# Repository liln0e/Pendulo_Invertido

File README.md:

# Péndulo Invertido Autocontrolado

Proyecto académico de un **péndulo invertido autocontrolado (self-balancing robot)** basado en **ESP32** y control **PID**, diseñado para mantener el equilibrio de forma autónoma mediante sensores inerciales y control en tiempo real.

---

## Descripción del proyecto

Este repositorio recoge el desarrollo de un **robot autoequilibrado de dos ruedas**, integrando diseño mecánico, electrónica y programación embebida.

El sistema utiliza un **ESP32** como unidad principal de control, un sensor **MPU6050** para estimar la inclinación y un controlador **PID** encargado de actuar sobre los motores para mantener el equilibrio.

El proyecto incluye:

- Diseño mecánico del chasis mediante modelado 3D.
- Diseño electrónico mediante una PCB personalizada en **KiCad**.
- Programación embebida sobre **ESP32**.
- Implementación de control **PID** para estabilidad del sistema.

---

## Tecnologías utilizadas

### Hardware

- ESP32 DevKitC  
- MPU6050  
- TB6612FNG  
- LM7805  
- Motores DC con reductora  
- PCB personalizada  
- Chasis impreso en 3D  

### Software y herramientas

- ESP32 / Arduino Framework  
- KiCad  
- Fusion 360  
- Control PID discreto  
- Filtro complementario  

---

## Estructura del repositorio

```txt
Proyecto_Pendulo_Invertido/
│
├── README.md
├── costes.md
├── documentacion.md
│
├── assets/
├── electronica/
├── mecanica/
└── software/
```

### Documentación principal

- [`documentacion.md`](./documentacion.md) → Explicación técnica completa del sistema.
- [`costes.md`](./costes.md) → Coste aproximado de materiales y componentes.

### Carpetas del proyecto

- [`electronica/`](./electronica/) → Diseño PCB y archivos de KiCad.
- [`mecanica/`](./mecanica/) → Diseño del chasis y fabricación.
- [`software/`](./software/) → Código del sistema de control.
- [`assets/`](./assets/) → Recursos visuales del proyecto.

---

## Integrantes del proyecto

### Carla Freire Muíño  
GitHub: [@carlafreeire](https://github.com/carlafreeire)

### Noelia Castro Rodríguez  
GitHub: [@liln0e](https://github.com/liln0e)

---

## Licencia

Proyecto desarrollado con fines académicos y educativos.

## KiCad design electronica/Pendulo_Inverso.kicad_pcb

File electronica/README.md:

# Diseño electrónico del péndulo invertido

Esta carpeta contiene los archivos del diseño electrónico del **péndulo invertido autocontrolado**, desarrollados en **KiCad**.

## Contenido

- `Pendulo_Inverso.kicad_sch` → Esquemático electrónico del sistema.
- `Pendulo_Inverso.kicad_pcb` → Diseño de la PCB.
- `Pendulo_Inverso.kicad_pro` → Proyecto completo de KiCad.

## Descripción

La electrónica integra los principales componentes del robot:

- **ESP32 DevKitC** como unidad de control.
- **MPU6050** para la medición de inclinación.
- **TB6612FNG** para el control de motores.
- **LM7805** para regulación de tensión.
- Conectores de alimentación y motores.

El diseño fue realizado sobre una **PCB personalizada** con el objetivo de reducir cableado, facilitar el ensamblaje y mejorar la integración del sistema.

La explicación técnica detallada puede consultarse en [`../documentacion.md`](../documentacion.md).

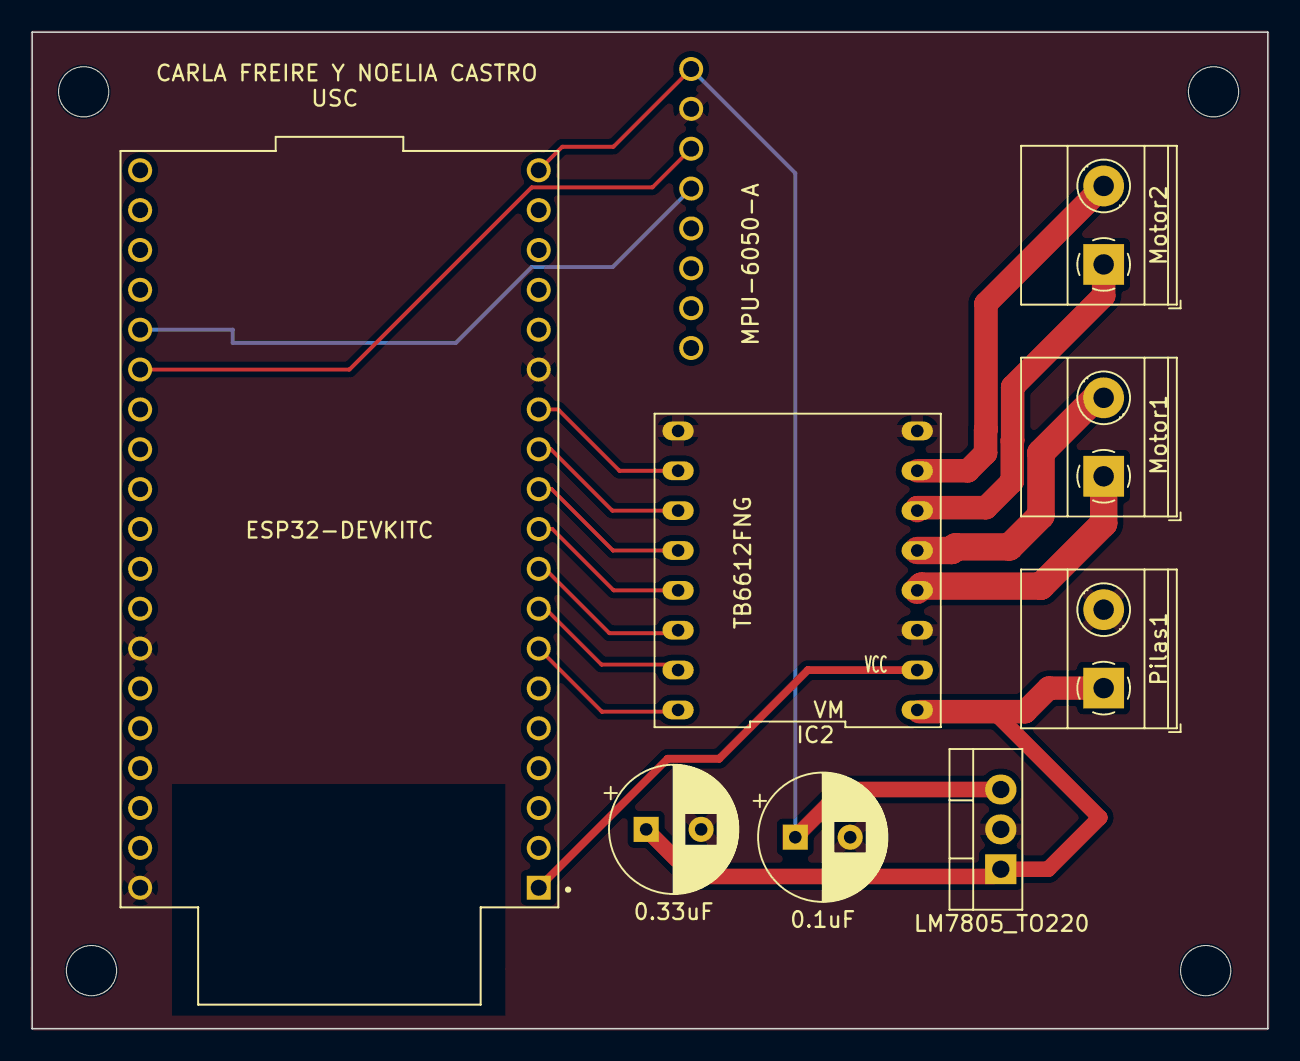
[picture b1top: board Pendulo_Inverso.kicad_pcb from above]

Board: 2 copper layers, 78.7 x 63.5 mm, 9 parts (0 on the bottom side), 17 nets.

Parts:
C2: 0.33uF; CP_Radial_D8.0mm_P3.50mm
C3: 0.1uF; CP_Radial_D8.0mm_P3.50mm
IC2: TB6612FNG; TB6612FngSparkfun
Motor1, Motor2: TerminalBlock_Phoenix_MKDS-1,5-2_1x02_P5.00mm_Horizontal
Pilas1: TerminalBlock_Phoenix_MKDS-1,5-2_1x02_P5.00mm_Horizontal
U1: LM7805_TO220; TO-220-3_Vertical
U2: ESP32-DEVKITC; MODULE_ESP32-DEVKITC
U4: MPU-6050-A; MPU6050

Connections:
AIN1: IC2.15 (AIN1), U2.8 (IO33)
AIN2: IC2.14 (AIN2), U2.9 (IO25)
AO1: IC2.4 (AO1), Motor1.1
AO2: IC2.5 (AO2), Motor1.2
BIN1: IC2.12 (BIN1), U2.11 (IO27)
BIN2: IC2.11 (BIN2), U2.12 (IO14)
BO1: IC2.6 (BO1), Motor2.1
BO2: IC2.7 (BO2), Motor2.2
GND: C2.2, C3.2, IC2.3 (GND), IC2.8 (GND), IC2.9 (GND), Pilas1.2, U1.2 (GND), U2.14 (GND1), U2.32 (GND2), U2.38 (GND3), U4.2 (GND)
unnamed: IC2.2 (VCC), U2.1 (3V3), U4.1 (VDD)
unnamed: C2.1, IC2.1 (VM1), Pilas1.1, U1.1 (VI)
unnamed: C3.1, U1.3 (VO), U2.19 (EXT_5V)
unnamed: U2.25 (IO0), U4.3 (SCL)
unnamed: U2.24 (IO2), U4.4 (SDA)
PWMA: IC2.16 (PWMA), U2.7 (IO32)
PWMB: IC2.10 (PWMB), U2.13 (IO12)
STBY: IC2.13 (STBY), U2.10 (IO26)

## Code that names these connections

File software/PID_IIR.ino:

#include <Wire.h>
#include <MPU6050.h>

MPU6050 mpu;

// ======================
// PINES ESP32
// ======================

#define SDA_PIN 32
#define SCL_PIN 33

#define PWMA 16
#define AIN2 17
#define AIN1 18

#define PWMB 22
#define BIN1 19
#define BIN2 21

#define STBY 23

const int freq = 20000;
const int resolution = 8;

const int channelA = 0;
const int channelB = 1;

// ======================
// VARIABLES MPU6050
// ======================

float accAngle = 0;
float gyroRate = 0;
float angle = 0;

unsigned long prevTime = 0;

// ======================
// PID COMO FILTRO IIR
// ======================

float setPoint = 0.0;

// Ganancias iniciales.
// Se pueden cambiar según las pruebas del robot.
float Kp = 18.0;
float Ki = 0.0;
float Kd = 0.8;

// Errores actual y anteriores.
float error0 = 0;   // e(k)
float error1 = 0;   // e(k-1)
float error2 = 0;   // e(k-2)

// Coeficientes del PID discreto en forma IIR.
float A0 = 0;
float A1 = 0;
float A2 = 0;

// Salida del controlador.
float output = 0;

int minPWM = 35;
int maxPWM = 255;

// ======================
// SETUP
// ======================

void setup() {

  Serial.begin(115200);

  Wire.begin(SDA_PIN, SCL_PIN);

  mpu.initialize();

  if (mpu.testConnection()) {
    Serial.println("MPU6050 conectado correctamente");
  } else {
    Serial.println("Error al conectar el MPU6050");
    while (1);
  }

  pinMode(AIN1, OUTPUT);
  pinMode(AIN2, OUTPUT);
  pinMode(BIN1, OUTPUT);
  pinMode(BIN2, OUTPUT);
  pinMode(STBY, OUTPUT);

  digitalWrite(STBY, HIGH);

  ledcSetup(channelA, freq, resolution);
  ledcSetup(channelB, freq, resolution);

  ledcAttachPin(PWMA, channelA);
  ledcAttachPin(PWMB, channelB);

  stopMotors();

  delay(1000);

  prevTime = millis();

  Serial.println("Sistema listo - PID IIR");
}

// ======================
// LOOP PRINCIPAL
// ======================

void loop() {

  int16_t ax, ay, az;
  int16_t gx, gy, gz;

  mpu.getMotion6(&ax, &ay, &az, &gx, &gy, &gz);

  unsigned long currentTime = millis();
  float dt = (currentTime - prevTime) / 1000.0;
  prevTime = currentTime;

  if (dt <= 0) dt = 0.001;

  // ======================
  // CÁLCULO DEL ÁNGULO
  // ======================

  accAngle = atan2(ay, az) * 180 / PI;
  gyroRate = gx / 131.0;

  angle = 0.98 * (angle + gyroRate * dt) + 0.02 * accAngle;

  // ======================
  // SEGURIDAD
  // ======================

  if (abs(angle) > 45) {
    stopMotors();
    resetPID();
    return;
  }

  // ======================
  // PID EN FORMA IIR
  // ======================

  // Actualizamos los coeficientes con el dt real.
  actualizarCoeficientes(dt);

  // Desplazamos los errores.
  // Lo que antes era e(k-1) pasa a ser e(k-2), etc.
  error2 = error1;
  error1 = error0;

  // Error actual.
  error0 = setPoint - angle;

  // Ecuación recursiva:
  // u(k) = u(k-1) + A0 e(k) + A1 e(k-1) + A2 e(k-2)
  output = output + A0 * error0 + A1 * error1 + A2 * error2;

  moveMotors(output);

  Serial.print("Angle: ");
  Serial.print(angle);

  Serial.print(" | Error: ");
  Serial.print(error0);

  Serial.print(" | PID IIR: ");
  Serial.println(output);

  delay(5);
}

// ======================
// CÁLCULO DE COEFICIENTES
// ======================

void actualizarCoeficientes(float dt) {

  // Estos coeficientes salen de discretizar el PID continuo.
  A0 = Kp + Ki * dt + Kd / dt;
  A1 = -Kp - 2.0 * Kd / dt;
  A2 = Kd / dt;
}

// ======================
// REINICIO DEL CONTROLADOR
// ======================

void resetPID() {

  error0 = 0;
  error1 = 0;
  error2 = 0;

  output = 0;
}

// ======================
// CONTROL DE MOTORES
// ======================

void moveMotors(float speed) {

  int pwm = abs(speed);

  pwm = constrain(pwm, 0, maxPWM);

  if (pwm > 0 && pwm < minPWM) {
    pwm = minPWM;
  }

  if (speed > 0) {

    digitalWrite(AIN1, HIGH);
    digitalWrite(AIN2, LOW);

    digitalWrite(BIN1, HIGH);
    digitalWrite(BIN2, LOW);

    ledcWrite(channelA, pwm);
    ledcWrite(channelB, pwm);
  }

  else if (speed < 0) {

    digitalWrite(AIN1, LOW);
    digitalWrite(AIN2, HIGH);

    digitalWrite(BIN1, LOW);
    digitalWrite(BIN2, HIGH);

    ledcWrite(channelA, pwm);
    ledcWrite(channelB, pwm);
  }

  else {
    stopMotors();
  }
}

// ======================
// PARAR MOTORES
// ======================

void stopMotors() {

  ledcWrite(channelA, 0);
  ledcWrite(channelB, 0);

  digitalWrite(AIN1, LOW);
  digitalWrite(AIN2, LOW);

  digitalWrite(BIN1, LOW);
  digitalWrite(BIN2, LOW);
}

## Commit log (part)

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2026-05-27 Revise README with project details and contributors
    Updated project description and added team members.
2026-05-27 Add README.md file
2026-05-27 Add README.md
2026-05-27 Add electronic design documentation for inverted pendulum
    Added detailed documentation for the electronic design of the inverted pendulum project, including schematics, PCB design, and component integration.
2026-05-27 Update README with mechanical design information
    Added detailed mechanical design documentation for the inverted pendulum project, including 3D models and design considerations.
2026-05-27 Enhance README with software details for inverted pendulum
    Added detailed documentation about the inverted pendulum software, including descriptions of various PID controller implementations and system functionalities.
2026-05-27 Update README with visual resources for project
    Added detailed project visual resources and descriptions.
2026-05-27 Add cost and materials documentation for robot project
    Document the estimated costs and materials for the self-balancing robot project, including a breakdown of components and total estimated cost.
2026-05-27 Agregar documentación técnica del proyecto
    Este documento proporciona una visión general del proyecto de péndulo invertido, incluyendo detalles sobre la arquitectura del sistema, diseño mecánico, electrónico y software. Se organizan los archi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
2026-05-27 Update GitHub username for Carla Freire Muíño
2026-05-27 Enhance README with electronic design details
    Updated the README to include electronic design in the project description.
2026-05-27 Mejorar la documentación técnica del proyecto
    Se actualizó la documentación técnica del proyecto para mejorar la claridad y precisión de la información sobre el diseño mecánico, electrónico y software del robot péndulo invertido.
